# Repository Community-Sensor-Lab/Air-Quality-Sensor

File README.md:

# Air Quality Sensor V4.5 CAD
### Most up-to-date CAD files for the Air Quality Sensor, including all mounts, stands and soldering tools.

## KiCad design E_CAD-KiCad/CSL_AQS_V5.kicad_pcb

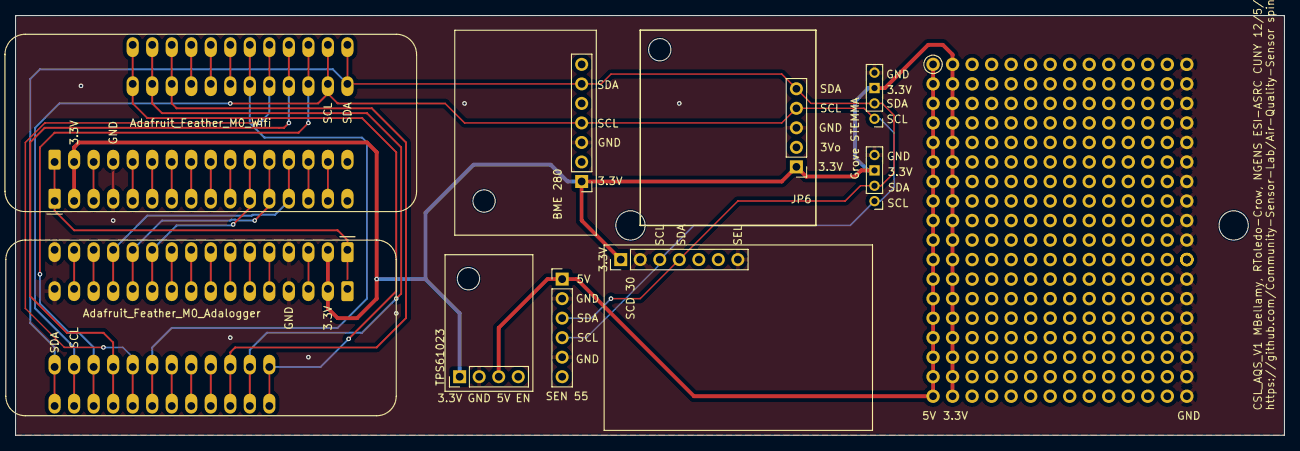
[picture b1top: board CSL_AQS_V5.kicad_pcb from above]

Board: 2 copper layers, 165.1 x 54.6 mm, 9 parts (0 on the bottom side), 13 nets.

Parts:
A1: Adafruit_Feather_M0_Wifi
A2: Adafruit_Feather_M0_Adalogger; Adafruit_Feather
J2, J3: Grove STEMMA; PinHeader_1x04_P2.00mm_Vertical
JP2: TPS61023; PinHeader_1x04_P2.54mm_Vertical
JP6: SCD41; PinHeader_1x05_P2.54mm_Vertical
JP7: BME280; PinHeader_1x07_P2.54mm_Vertical
JP8: SEN 55; PinHeader_1x06_P2.54mm_Vertical
JP10: SCD 30; PinHeader_1x07_P2.54mm_Vertical

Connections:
3.3V: A1.2 (3V3), A2.2 (3V3), J2.3, J3.3, JP2.1, JP6.1, JP7.1, JP10.1
5V: JP2.3, JP8.1
GND: A1.4 (GND), A2.4 (GND), A2.16 (GND), J2.4, J3.4, JP2.2, JP6.3, JP7.3, JP8.2, JP8.5, JP10.2, JP10.7
NC: JP7.5, JP8.6
unnamed: A1.22 (D10), A2.22 (D10)
unnamed: A1.27 (EN), A2.27 (EN)
unnamed: A1.13 (MISO/D22), A2.13 (MISO/D22)
unnamed: A1.12 (MOSI/D23), A2.12 (MOSI/D23)
unnamed: A1.11 (SCK/D24), A2.11 (SCK/D24)
unnamed: A1.26 (USB), A2.26 (USB)
unnamed: A1.28 (VBAT), A2.28 (VBAT)
SCL: A1.18 (SCL/D21), A2.18 (SCL/D21), J2.1, J3.1, JP6.4, JP7.4, JP8.4, JP10.3
SDA: A1.17 (SDA/D20), A2.17 (SDA/D20), J2.2, J3.2, JP6.5, JP7.6, JP8.3, JP10.4

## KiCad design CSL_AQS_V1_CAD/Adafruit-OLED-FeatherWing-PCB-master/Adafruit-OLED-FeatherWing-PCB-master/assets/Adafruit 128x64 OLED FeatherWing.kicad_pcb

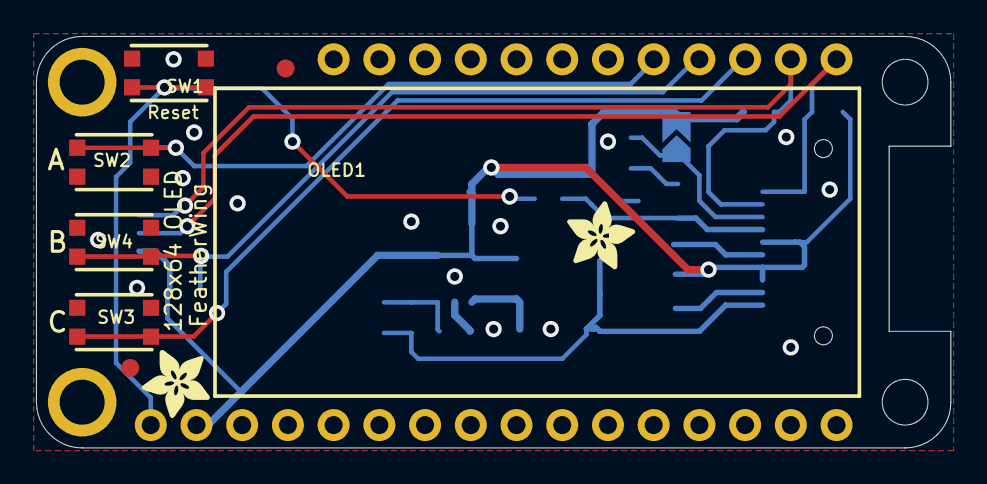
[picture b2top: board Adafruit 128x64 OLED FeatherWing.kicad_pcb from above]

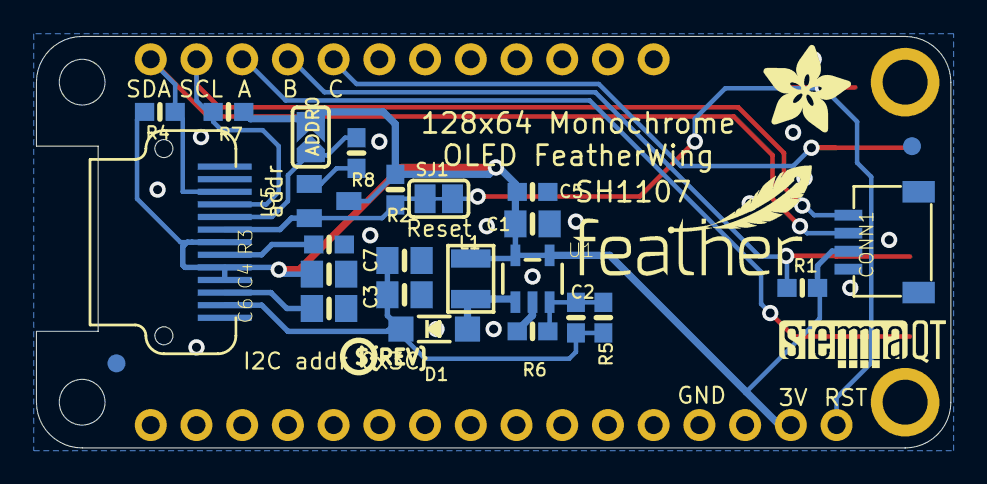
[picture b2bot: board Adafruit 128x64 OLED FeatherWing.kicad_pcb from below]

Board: 2 copper layers, 50.8 x 22.9 mm, 38 parts (28 on the bottom side), 15 nets.

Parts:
ADDR0: SOLDERJUMPER_ARROW_NOPASTE
C1, C4, C6: 10uF; 0805-NO
C2, C5: 0.1uF; 0603-NO
C3, C7: 10uF/16V; 0805-NO
CONN1: STEMMA_I2C_QT; JST_SH4
D1: MBR120; SOD-123
FID1, FID2, FID3, FID4: FIDUCIAL_1MM
IC5: APX803; SOT23
L1: 10uH; INDUCTOR_1007
MS1: FEATHERWING_NODIM
OLED1: OLED_128X64_SH1107; QT1107P11A
R1, R5: 100K; 0603-NO
R2, R6, R8: 12K; 0603-NO
R3: 680K; 0603-NO
R4, R7: 2.2K; 0603-NO
SJ1: SOLDERJUMPER_CLOSEDWIRE
SW1, SW2, SW3, SW4: KMR2; BTN_KMR2_4.6X2.8
U1: FAN5331SX; SOT23-5
U$8: ADAFRUIT_5MM
U$14: PCBFEAT-REV-040
U$16, U$37: ADAFRUIT_3.5MM
U$35: STEMMAQT
U$36: FEATHERLOGO_SMALL

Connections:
3.3V: ADDR0.2, C1.1, C4.2, C5.2, CONN1.2, IC5.3, L1.P$1, MS1.2, OLED1.4, OLED1.5, OLED1.7, R1.2, R2.2, R4.2, R7.2, U1.4, U1.5
+12V: C2.1, C3.1, C7.1, D1.C, OLED1.2, R5.2
GND: C1.2, C3.2, C4.1, C5.1, C6.1, C7.2, CONN1.1, CONN1.MT1, CONN1.MT2, IC5.1, MS1.4, OLED1.1, OLED1.12, OLED1.13, R3.1, R6.1, R8.1, SW1.A, SW1.A', SW2.A, SW2.A', SW3.A, SW3.A', SW4.A, SW4.A', U1.2
H: MS1.19, SW3.B, SW3.B'
I: MS1.20, R1.1, SW4.B, SW4.B'
J: MS1.21, SW2.B, SW2.B'
unnamed: D1.A, L1.P$2, U1.1
unnamed: ADDR0.1, OLED1.9, R8.2
unnamed: C2.2, R5.1, R6.2, U1.3
unnamed: OLED1.6, R3.2
SCL: CONN1.4, MS1.18, OLED1.10, R7.1
SDA: CONN1.3, MS1.17, OLED1.11, R4.1
VCOMH: C6.2, OLED1.3
~OLED_RST: IC5.2, OLED1.8, R2.1, SJ1.2
~RESET: MS1.1, SJ1.1, SW1.B, SW1.B'

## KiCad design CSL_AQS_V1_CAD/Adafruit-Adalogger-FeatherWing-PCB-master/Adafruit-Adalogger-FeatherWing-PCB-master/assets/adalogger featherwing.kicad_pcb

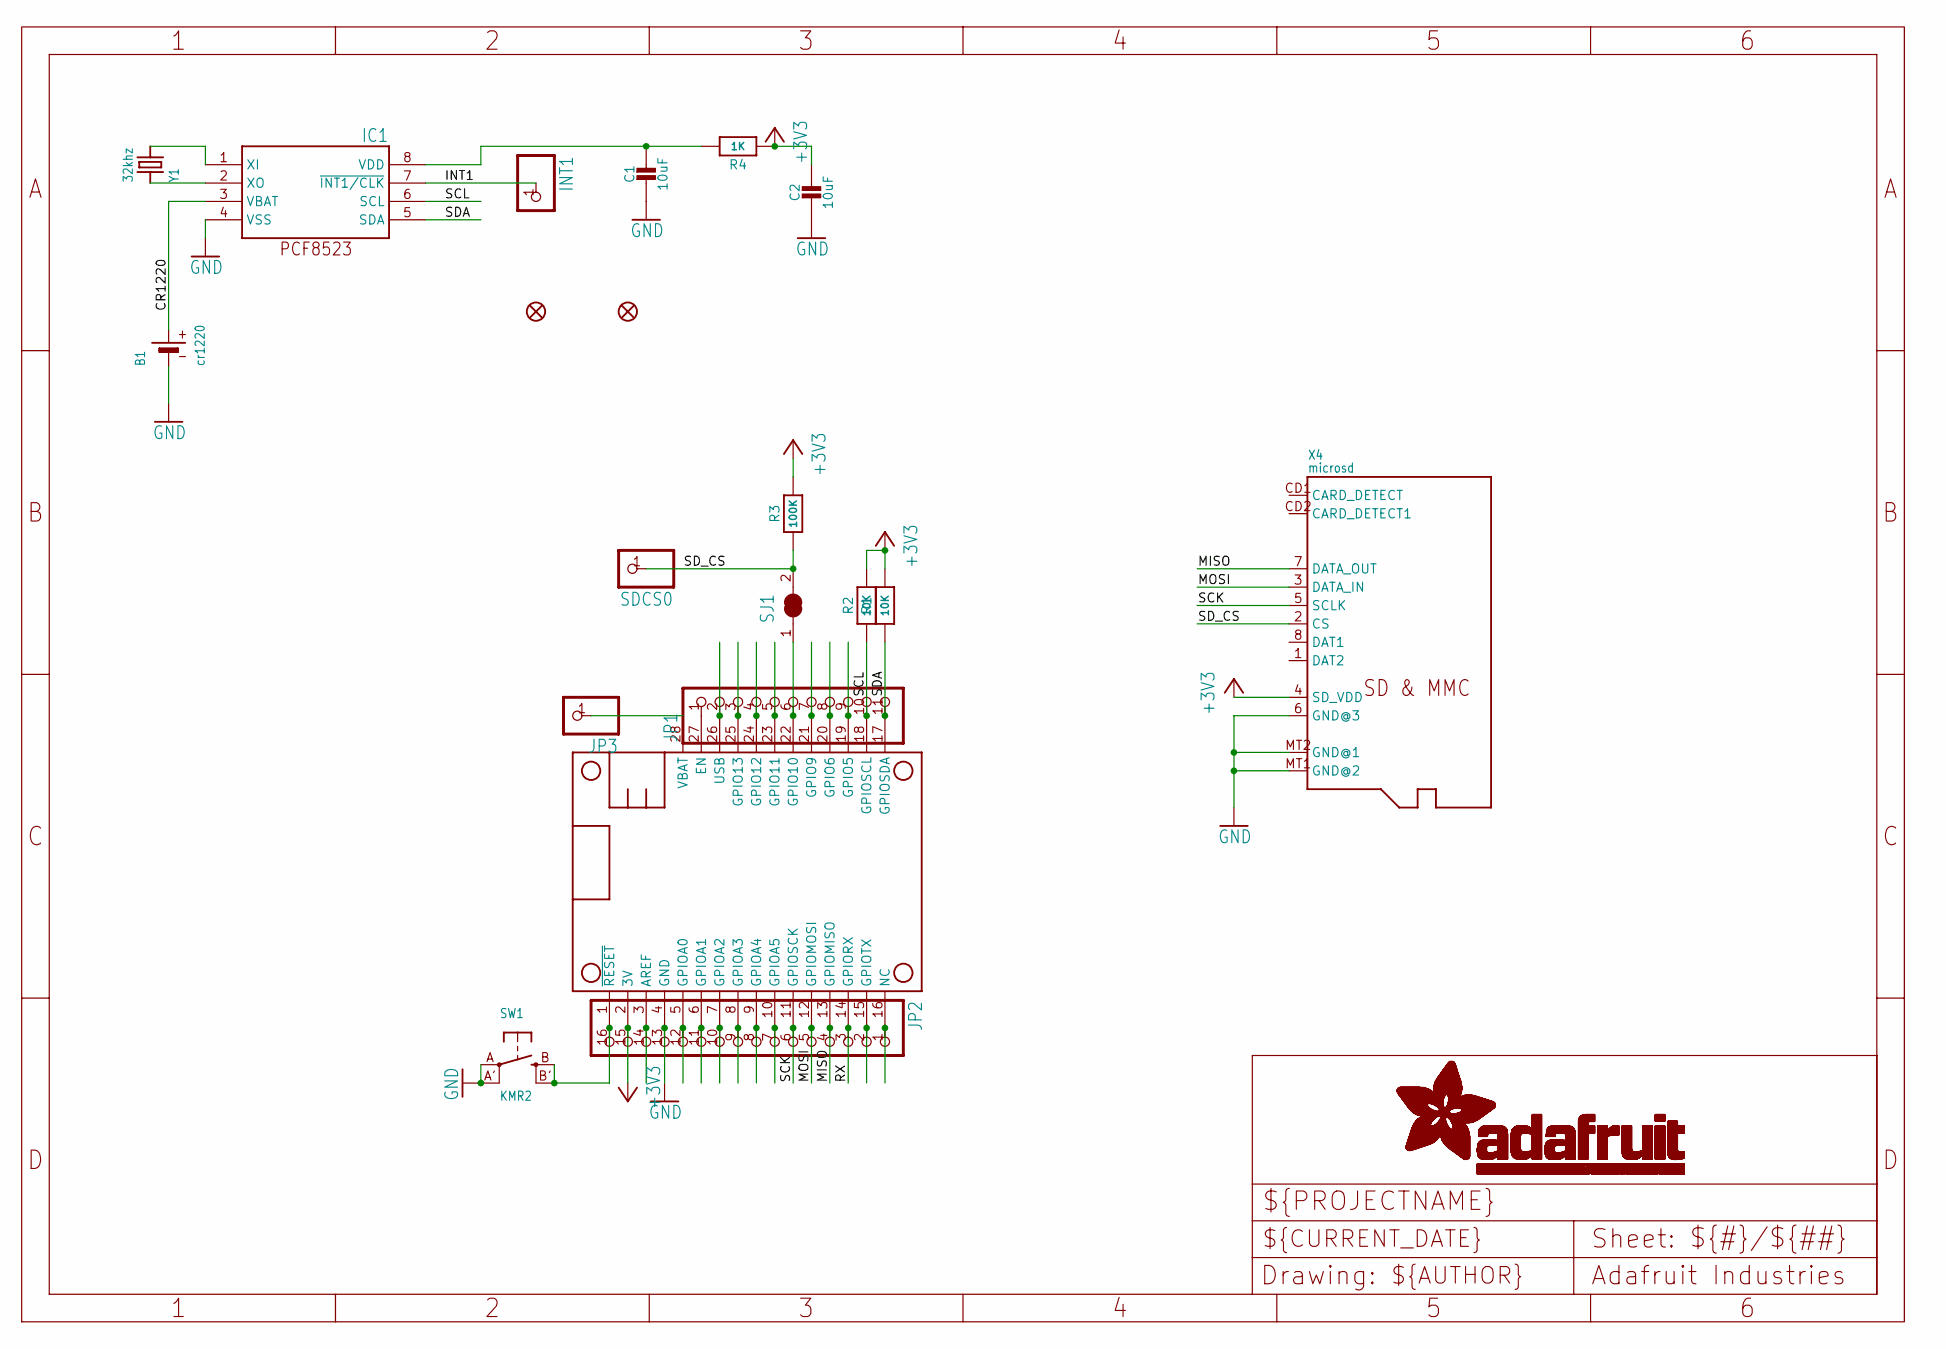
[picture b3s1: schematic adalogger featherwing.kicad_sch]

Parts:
B1: cr1220; CR1220-2
C1, C2: 10uF; 0805-NO
FID1, FID2: FIDUCIAL_1MM
IC1: RTC_PCF8523T; SOIC8_150MIL
INT1: HEADER-1X1ROUND; 1X01_ROUND
JP1: HEADER-1X11; 1X11_ROUND
JP2: HEADER-1X16ROUND; 1X16_ROUND
JP3: HEADER-1X1ROUND; 1X01_ROUND
MS1: FEATHERWING_NODIM
R1, R2: 10K; 0603-NO
R3: 100K; 0603-NO
R4: 1K; 0603-NO
SDCS0: HEADER-1X1ROUND; 1X01_ROUND
SJ1: SOLDERJUMPER_CLOSED; SOLDERJUMPER_CLOSEDWIRE
SW1: KMR2; BTN_KMR2_4.6X2.8
X4: microsd; MICROSD
Y1: 32khz; CRYSTAL_8X3.8

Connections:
+3V3: C2.1, JP2.15, MS1.2 (3V), R1.2, R2.2, R3.2, R4.1, X4.4 (SD_VDD)
A: JP2.12, MS1.5 (GPIOA0)
AREF: JP2.14, MS1.3 (AREF)
B: JP2.11, MS1.6 (GPIOA1)
C: JP2.10, MS1.7 (GPIOA2)
CR1220: B1.+, IC1.3 (VBAT)
CS: JP1.6, MS1.22 (GPIO10), SJ1.1
D: JP2.9, MS1.8 (GPIOA3)
E: JP2.8, MS1.9 (GPIOA4)
EN: JP1.1, MS1.27 (EN)
F: JP2.7, MS1.10 (GPIOA5)
G: JP2.1, MS1.16 (NC)
GND: B1.-, C1.2, C2.2, IC1.4 (VSS), JP2.13, MS1.4 (GND), SW1.A, SW1.A' (P1), X4.6 (GND@3), X4.MT1 (GND@2), X4.MT2 (GND@1)
H: JP1.9, MS1.19 (GPIO5)
I: JP1.8, MS1.20 (GPIO6)
INT1: IC1.7 (~INT1/CLK), INT1.1
J: JP1.7, MS1.21 (GPIO9)
L: JP1.5, MS1.23 (GPIO11)
M: JP1.4, MS1.24 (GPIO12)
MISO: JP2.4, MS1.13 (GPIOMISO), X4.7 (DATA_OUT)
MOSI: JP2.5, MS1.12 (GPIOMOSI), X4.3 (DATA_IN)
N: JP1.3, MS1.25 (GPIO13)
unnamed: C1.1, IC1.8 (VDD), R4.2
unnamed: IC1.1 (XI), Y1.P$4 (2)
unnamed: IC1.2 (XO), Y1.P$1 (1)
RESET: JP2.16, MS1.1 (~RESET), SW1.B (S), SW1.B' (S1)
RX: JP2.3, MS1.14 (GPIORX)
SCK: JP2.6, MS1.11 (GPIOSCK), X4.5 (SCLK)
SCL: IC1.6 (SCL), JP1.10, MS1.18 (GPIOSCL), R2.1
SDA: IC1.5 (SDA), JP1.11, MS1.17 (GPIOSDA), R1.1
SD_CS: R3.1, SDCS0.1, SJ1.2, X4.2 (CS)
TX: JP2.2, MS1.15 (GPIOTX)
USB: JP1.2, MS1.26 (USB)
VBAT: JP3.1, MS1.28 (VBAT)

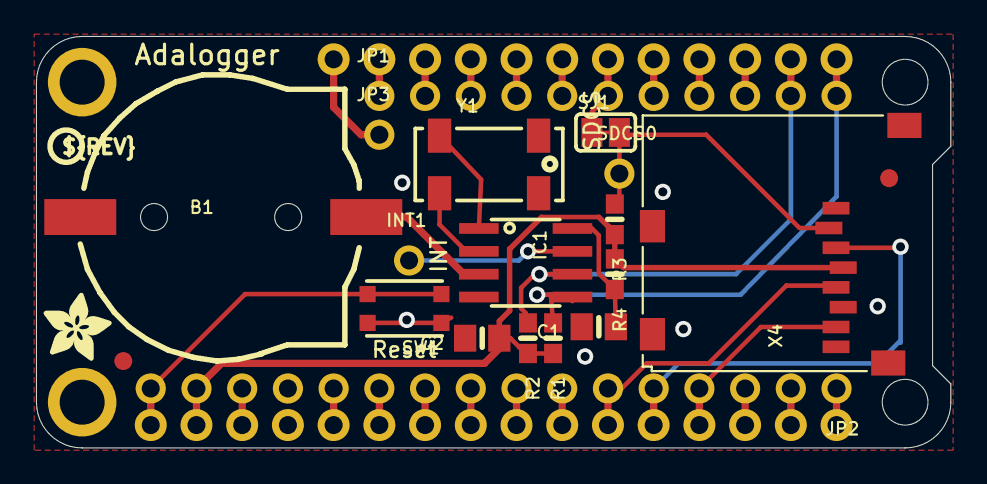
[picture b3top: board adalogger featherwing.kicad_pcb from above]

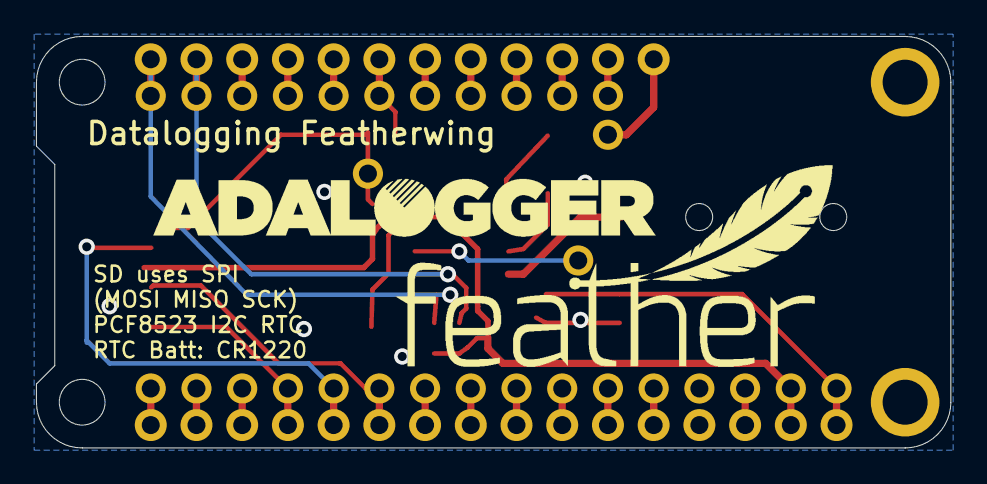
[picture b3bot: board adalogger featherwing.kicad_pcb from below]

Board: 2 copper layers, 50.8 x 22.9 mm, 24 parts (2 on the bottom side), 34 nets.

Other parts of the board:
U$2: FEATHERLOGO
U$3: ADALOGGER_LOGO
U$4: ADAFRUIT_3.5MM
U$5: PCBFEAT-REV-040

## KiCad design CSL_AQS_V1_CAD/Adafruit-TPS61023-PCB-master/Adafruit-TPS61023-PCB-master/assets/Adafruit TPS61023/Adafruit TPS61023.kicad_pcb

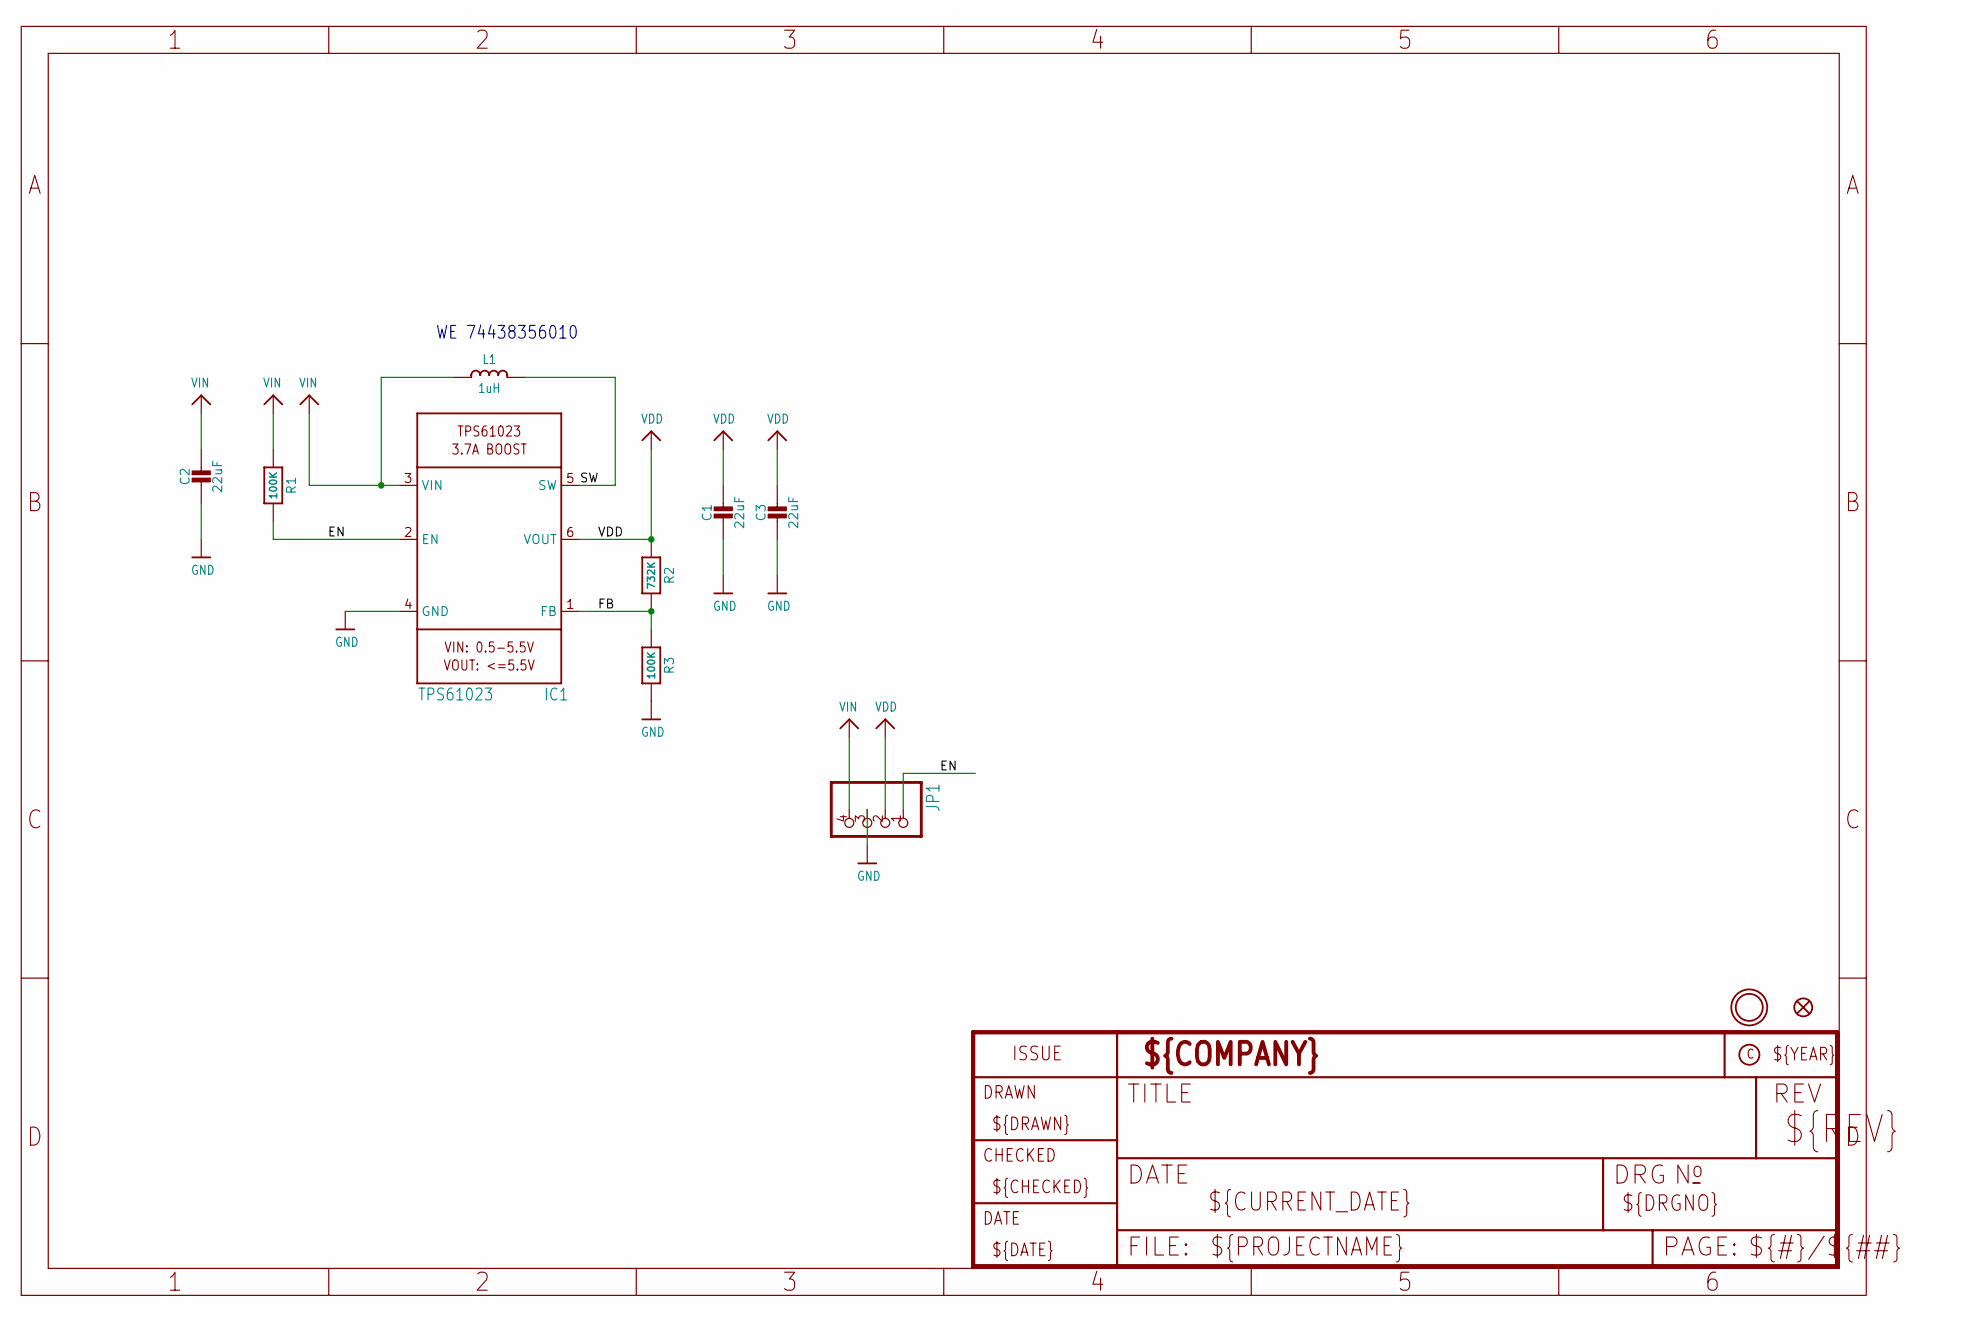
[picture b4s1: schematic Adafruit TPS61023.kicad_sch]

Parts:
C1, C2, C3: 22uF; 0805-NO
FID1: FIDUCIAL_1MM
IC1: TPS61023; SOT563
JP1: HEADER-1X4ROUND; 1X04_ROUND
L1: 1uH; INDUCTOR_5X5MM_TDK_VLC5045
R1, R3: 100K; 0603-NO
R2: 732K; 0603-NO
U$9: MOUNTINGHOLE2.5; MOUNTINGHOLE_2.5_PLATED

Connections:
EN: IC1.2 (EN), JP1.1, R1.2
FB: IC1.1 (FB), R2.2, R3.1
GND: C1.2, C2.2, C3.2, IC1.4 (GND), JP1.3, R3.2
SW: IC1.5 (SW), L1.P$2 (2)
VDD: C1.1, C3.1, IC1.6 (VOUT), JP1.2, R2.1
VIN: C2.1, IC1.3 (VIN), JP1.4, L1.P$1 (1), R1.1

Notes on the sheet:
WE 74438356010

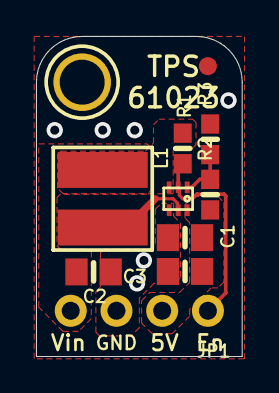
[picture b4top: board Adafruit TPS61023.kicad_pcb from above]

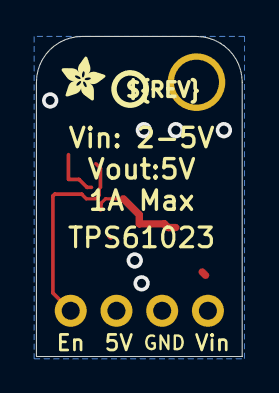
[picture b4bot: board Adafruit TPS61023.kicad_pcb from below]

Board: 2 copper layers, 11.4 x 17.8 mm, 13 parts (2 on the bottom side), 6 nets.

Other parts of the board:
U$10: PCBFEAT-REV-040
U$11: ADAFRUIT_2.5MM

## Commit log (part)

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2025-06-07 Update Readme.md
    Removed all the verbose sub-bullets
    Clean numbering - consistent formatting with proper sequence (including 3.5)
    Clear titles - used the actual document titles from the links
    Author credits - kept in parentheses but cleaner format
    Hidden the notes - moved to HTML comments so they're not visible to users but still accessible to the team
    README-DETAILED.md - links to comprehensive version with all the detailed breakdowns
2025-06-07 README-DETAILED
    Comprehensive version with all the detailed breakdowns
2025-06-07 README-DETAILED.md
    Comprehensive version with all the detailed breakdowns
2025-06-07 Readme.md
    Removed all the verbose sub-bullets
    Clean numbering - consistent formatting with proper sequence (including 3.5)
    Clear titles - used the actual document titles from the links
    Author credits - kept in parentheses but cleaner format
    Hidden the notes - moved to HTML comments so they're not visible to users but still accessible to the team
    README-DETAILED.md - Links to the verbose version with all sub-bullets and explanations
2025-06-07 Readme.md
    Removed all verbose sub-bullets
    Clean numbering - consistent formatting with proper sequence (including 3.5)
    Clear titles - used the actual document titles from the links
    Author credits - kept in parentheses but cleaner format
    Hidden the notes - moved to HTML comments so they're not visible to users but still accessible to the team
    README-DETAILED.md - Linked to the verbose version with all sub-bullets and explanations
2025-06-10 Converted from Google Sheets to Markdown
    Switched from Google Sheets to Markdown for structured data storage
    Updated file paths to relative references for portability and simplicity
2025-06-10 Centralized to contents folder
2025-06-10 testing preview
2025-06-11 updated some images in parts list
2025-06-11 more images fix'd
2025-06-11 moved images folder
2025-06-11 Renamed folder to guides
2025-06-13 Added .gitignore to exclude system files
2025-06-13 Remove Documents/Air-Quality-Sensor folder
2025-06-13 Update image sizes and make them clickable
2025-06-13 Refactored soldering guide and restructured layout
2025-06-13 Restructure Arduino installation guide
2025-06-13 Add hover links and improve image placement in soldering guide
    - Added links to component datasheets and supplier pages
    - Included brief descriptions for key sensors (BME280, SCD41)
    - Added tool reference links for community builders
    - Moved component layout image to logical position after materials list
    - Added image caption for better context
2025-06-14 Restructure Feather M0 WiFi setup guide - Add logical section hierarchy and clear headings - Group related steps for better flow - Add hover links to components and resources - Include troubleshootin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
2025-06-14 docs: reorganize sensor assembly guide with improved structure and flow
    - Add logical section hierarchy and clear progression
    - Group materials by category with helpful reference links
    - Move preliminary setup steps before sensor assembly
    - Standardize testing procedures across all sensors
    - Add safety warnings and best practices section
    - Improve visual formatting while preserving all original content
2025-06-14 Restructure sensor code activity README for improved flow and accessibility
2025-06-14 Enhance sensor building guide with clear headings and helpful links
2025-06-14 Enhance AQS documentation for better community engagement and usability
2025-06-14 Resource Section: Added links to documentation and community resources
    Next Steps: Explains what happens after setup completion
    Troubleshooting: Comprehensive problem-solving section
2025-06-14 Graphs: Added missing images
2025-06-14 Improve README: reorganize AQS assembly steps, fix typos, add supplier links
2025-06-14 Adjusting image size
2025-06-14 docs: enhance README with professional formatting and badges
2025-06-14 docs: enhance README-DETAILED with professional formatting and badges
2025-06-15 added CSL banner
2025-06-15 Remove hyperlinks
2025-06-15 Remove style tags
2025-06-15 Updated Parts-List. Remove style tags
2025-06-15 test
2025-06-15 Resized Part-List images
2025-06-15 Add hero image
2025-06-15 Add hero images
2025-06-16 added new readme image
2025-06-16 added 9.8 Assembley of AQS Monitor on PCB Board
2025-06-17 Saving uncommitted changes before rebase
2025-06-17 Update of MCAD Files
2025-06-17 new hero image
2025-06-17 new detailed readme hero image
2025-06-18 Added remoteSamplingUpdate functionality
2025-06-19 fixed json in request
2025-06-19 adding description to functions
2025-06-20 Update CSL_AQS_V5.ino
    updated for loop to work as delay for using sampleTime and watchdogs return value. Current assumption is that watch dog returns 8000 every time. So the minimum sampling rate is 8000. Anything below 8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
2025-06-20 Update CSL_AQS_V5.ino
    Testing remotely turning off the screen
2025-06-20 Update CSL_AQS_V5.ino
    Testing remotely switching the screen off
2025-06-20 Update CSL_AQS_V5.ino
    Comment out
2025-06-20 Update payloadUpload.ino
    Leaving a comment to remember about implementing the remotely turning the screen feature
2025-06-20 Create CSL_AQS_V5.h
    Adding header file to simplify code in AQS_CSL_V5.ino
2025-06-20 finished setting watch dog minimum time is 16 seconds. This can be changed using delay().
2025-06-21 Moved dependencies to heder file and cleaned sensor print by turning into a function located in initalizedOLED.ino
2025-06-21 added description to BME and moved provision html to header file
2025-06-21 Update provision.ino
    Document prisioning
2025-06-27 updated payload upload to disconnect from wifi only if the sampling rate is below 5 seconds. This increased speed by 3 seconds on average.
2025-06-27 updated the header for the sd file to include samplingTime and WiFi status.
2025-06-27 clear screen after connecting to wifi
2025-06-27 pre testing watch dog
2025-06-27 finished setting setting up watch dog. The default sleep time for watch dog is 16ms and our sensor base time is 20 seconds.
2025-06-27 cleaning post watchdog integration
2025-06-30 Update initializeOLED.ino
    cleaned displaySensorData fuction to use printf
2025-06-30 Update CSL_AQS_V5.ino
    fixed displaySensorData call
2025-06-30 Update payloadUpload.ino
    fixed sd write message
2025-06-30 Update initializeOLED.ino
    Added an interrupt to clear the screen
2025-06-30 simplified tempString expression and shorten sensors read return value.
2025-07-02 updated sensor return
2025-07-02 repaired blank screen mode
2025-07-03 Update of AQS Mount CAD
    Changed Naming and Included New Versions of Mounts
2025-07-07 Added new images
    Sticker compositions
2025-07-07 Update Readme.md
    Lab sticker composition added
2025-07-07 Update README-DETAILED.md
    Roof sticker composite
2025-07-07 keep the toggleButton() and keep original provisioning
2025-07-07 keep original provision html file
2025-07-07 Update CSL_AQS_V5.ino
    commented out scd30 library and fixed force_pro reference
2025-07-07 Update CSL_AQS_V5.ino
    removed unnecessary delayed required for the scd30 and updated the output.
2025-07-07 Update appscript_google.js
    Corrected variable name place holder
2025-07-07 re added delay after pinMode to stabilize the button (A).
2025-07-10 Update of CAD + New Assembly
    Updated Air Quality Sensor Mount Assembly. As well as included a new Assembly with all Sensors and Parts included.
2025-07-10 Update CAD and ReadMe
    Improved Readme and created STP so older versions of Inventor can load them. As well as moved STL files to their own folder for easy access.
2025-07-15 Delete SEN5X Mount 4.stl
    removed duplicate STL
2025-07-17 Update of CAD
    Removed Useless files and added new files
2025-07-24 Update of Images and CAD
    Included Solar Board and Battery Mounting. With updated Images to match new mounting.
2025-08-25 Added provision flowchart image
2025-08-25 Add ESP32 provisioning flowchart image
2025-08-25 Remove outdated flowchart and add ESP32 provisioning reference
2025-08-25 Add ESP32 provisioning flowchart reference after Step 10
2025-08-25 Credit Fahmin for ESP32 provisioning flowchart in README
2025-08-27 Update README-DETAILED 3.5 with Fahmin's flowchart credit
2025-09-08 Update Readme.md
    professional to printed
2025-11-14 Updated E-CAD File
    Revisited a missed connection in the E-CAD files. Placement of the OLED when resetting should now function regardless of the board it is stacked on.
2025-12-01 Update to PCB Connections
    Connected reset pins of Adafruit logger and microcontroller
2025-12-01 Added E_CAD files for PCB
2025-12-05 Add M_CAD Folder
    Moved over M_CAD folder from branch to main
    Added antenna mount in M_CAD folder
2025-12-05 Antenna
    Added the READme and corresponding images for the new antenna addition to the AQS system
2025-12-05 Moved Antenna Readme Location
2025-12-05 Reverted Antenna Location
2025-12-05 Created Antenna Folder w/ Images
2026-02-13 CSL_AQS_V5_timing
    Optimization of SEN55x:
    -Incorporated idle, partial, and full measurement modes
    -Shifted some code to minimize current consumption
2026-04-16 Clear Bus
    Testing a wire end begin fix to clear the system I2C bus on every loop
2026-04-16 MacAddress Testing
2026-04-16 Removed files testing different factors
2026-04-16 Mac Address Testing
2026-05-01 Enabled Soft Reset
    Checks BME data. If outside BME limits the system resets
2026-05-04 Removed Extra Files
    Replaced Old CSL_AQS_V5 file with SensorReset renamed to CSL_AQS_V5
2026-05-04 Renamed MacAddress file to CSL_AQS_V5
2026-05-04 Renamed Timing File to CSL_AQS_V5
2026-06-02 Additional Debug Info
    WiFi strength and a connection to google servers will now be logged on the microSD card. Additionally code base has sensor reset and mac address code incorporated
2026-06-02 Transmits Wifi Strength and Device Mac Address
2026-06-03 Restructured Mac Address Position
    Restructured the Position Mac Address is read from provision to payload
2026-06-04 Updated Displayed MacAddress
2026-06-04 System now displays MacAddress
